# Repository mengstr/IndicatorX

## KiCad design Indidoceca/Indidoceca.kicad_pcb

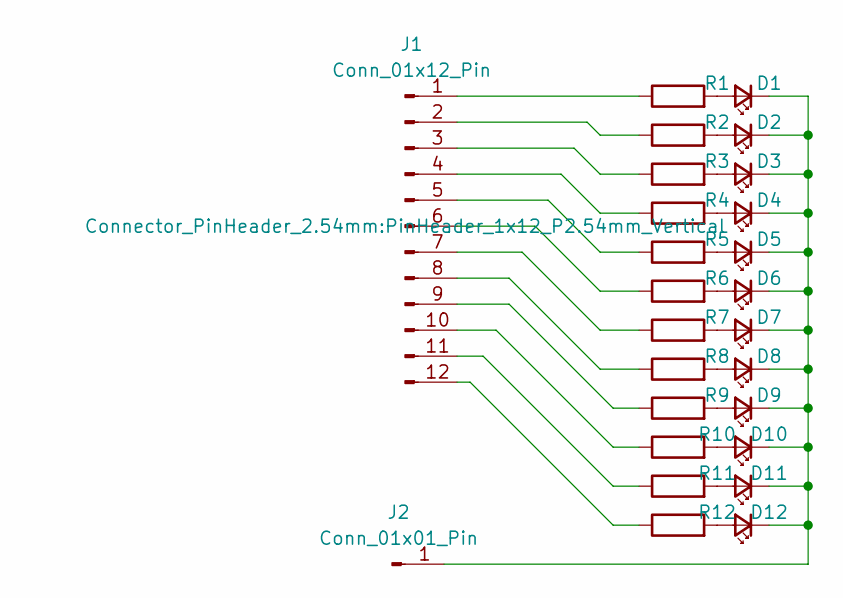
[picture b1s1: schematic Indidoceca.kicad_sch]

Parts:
D1, D2, D3, D4, D5, D6, D7, D8, D9, D10, D11, D12: LED_Small; LED_0603_1608Metric
J1: Conn_01x12_Pin; PinHeader_1x12_P2.54mm_Vertical
J2: Conn_01x01_Pin; PinHeader_1x01_P2.54mm_Vertical
R1, R2, R3, R4, R5, R6, R7, R8, R9, R10, R11, R12: R; R_0603_1608Metric

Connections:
unnamed: D1.2 (A), R1.2
unnamed: D1.1 (K), D2.1 (K), D3.1 (K), D4.1 (K), D5.1 (K), D6.1 (K), D7.1 (K), D8.1 (K), D9.1 (K), D10.1 (K), D11.1 (K), D12.1 (K), J2.1
unnamed: D2.2 (A), R2.2
unnamed: D3.2 (A), R3.2
unnamed: D4.2 (A), R4.2
unnamed: D5.2 (A), R5.2
unnamed: D6.2 (A), R6.2
unnamed: D7.2 (A), R7.2
unnamed: D8.2 (A), R8.2
unnamed: D9.2 (A), R9.2
unnamed: D10.2 (A), R10.2
unnamed: D11.2 (A), R11.2
unnamed: D12.2 (A), R12.2
unnamed: J1.1, R1.1
unnamed: J1.2, R2.1
unnamed: J1.3, R3.1
unnamed: J1.4, R4.1
unnamed: J1.5, R5.1
unnamed: J1.6, R6.1
unnamed: J1.7, R7.1
unnamed: J1.8, R8.1
unnamed: J1.9, R9.1
unnamed: J1.10, R10.1
unnamed: J1.11, R11.1
unnamed: J1.12, R12.1

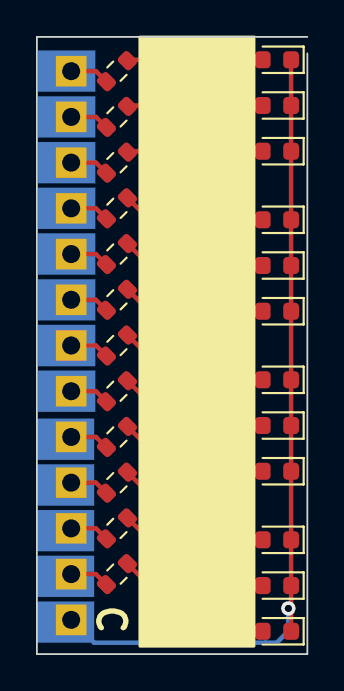
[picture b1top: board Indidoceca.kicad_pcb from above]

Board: 2 copper layers, 15.0 x 34.3 mm, 26 parts (0 on the bottom side), 25 nets.
